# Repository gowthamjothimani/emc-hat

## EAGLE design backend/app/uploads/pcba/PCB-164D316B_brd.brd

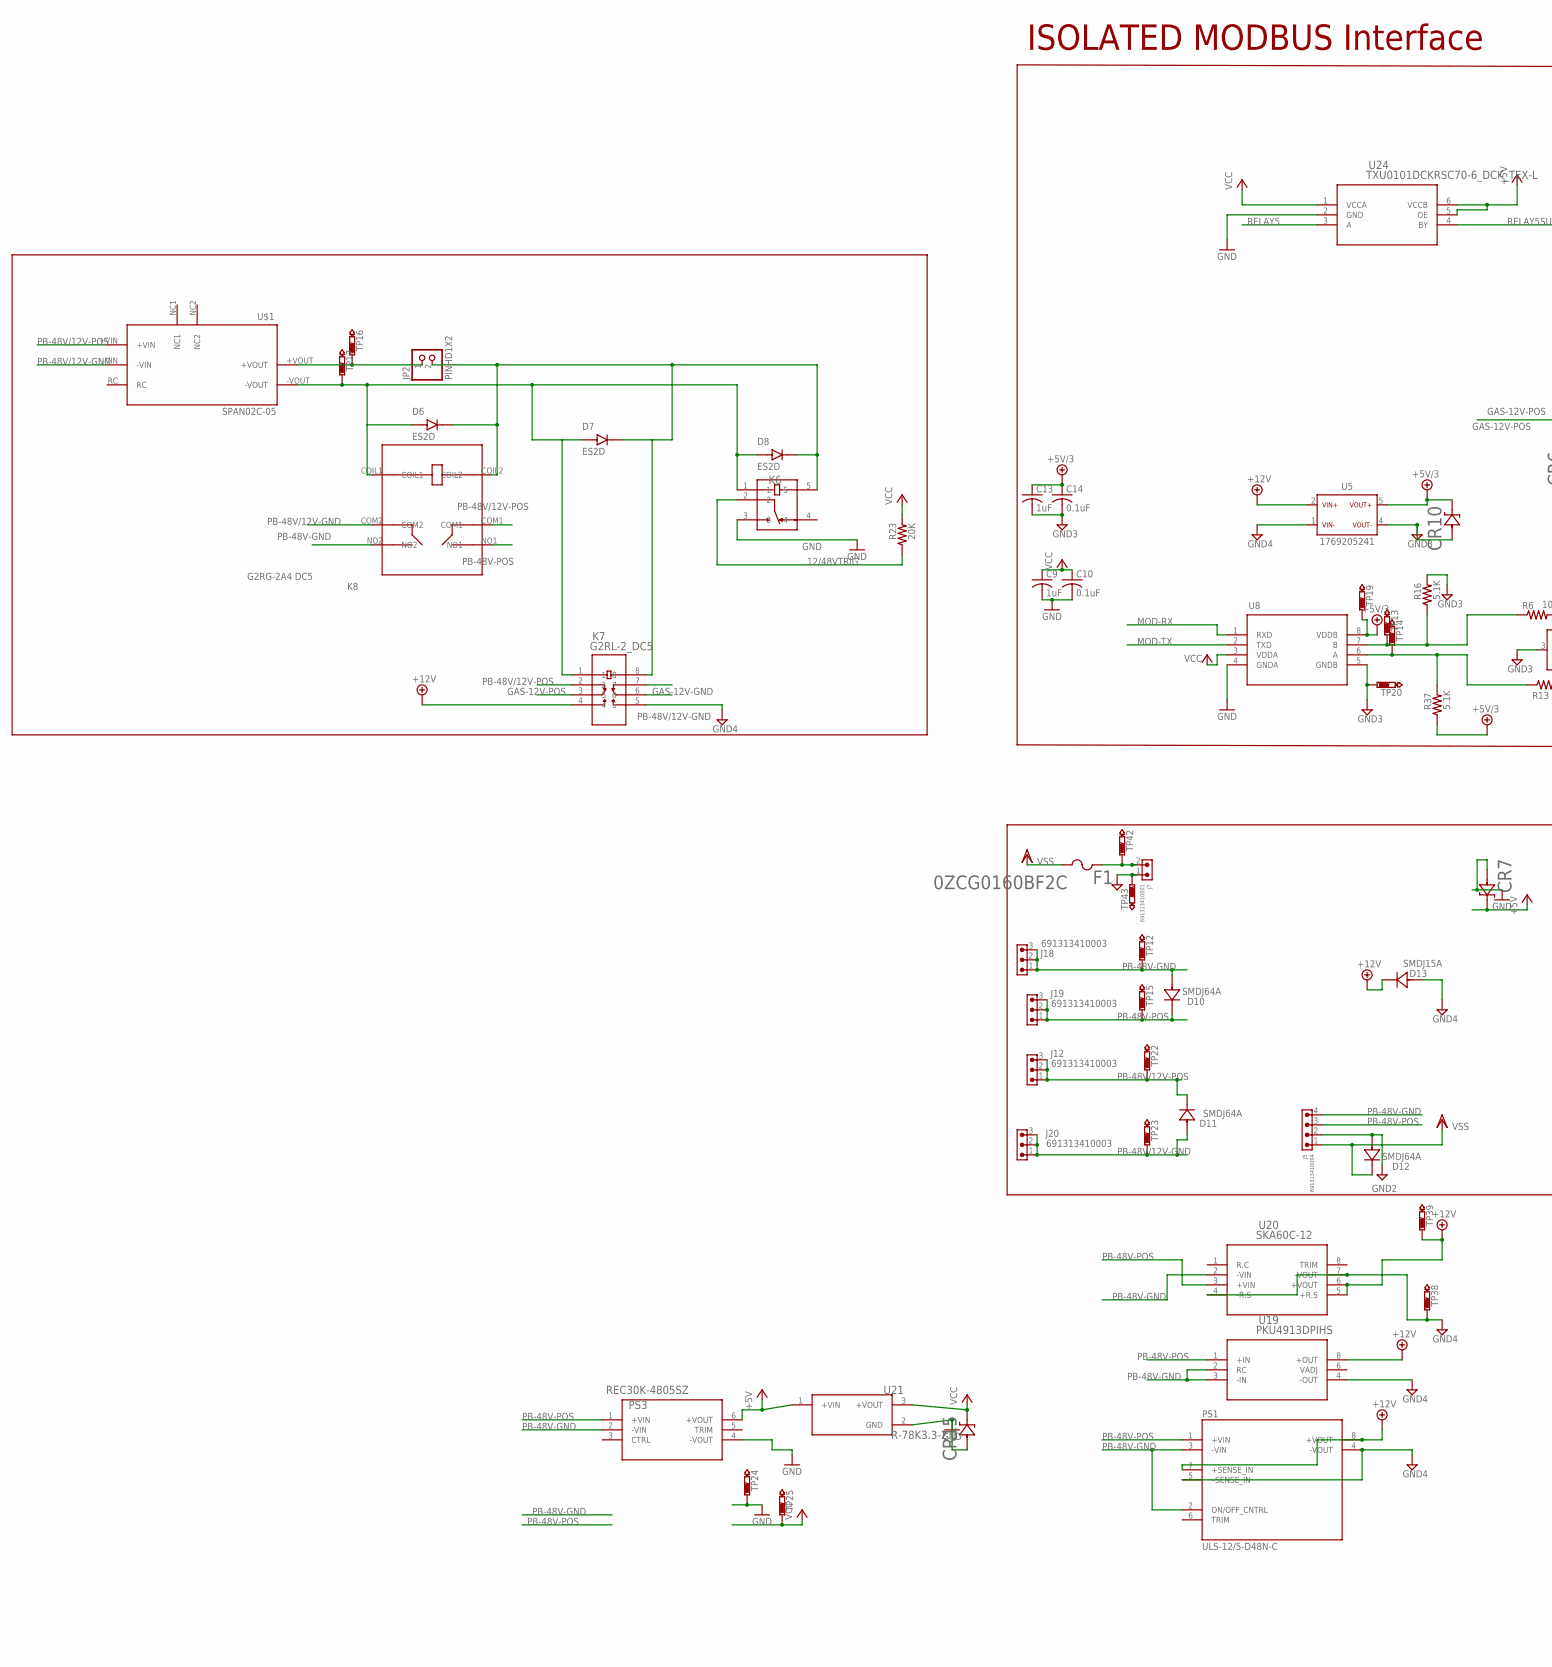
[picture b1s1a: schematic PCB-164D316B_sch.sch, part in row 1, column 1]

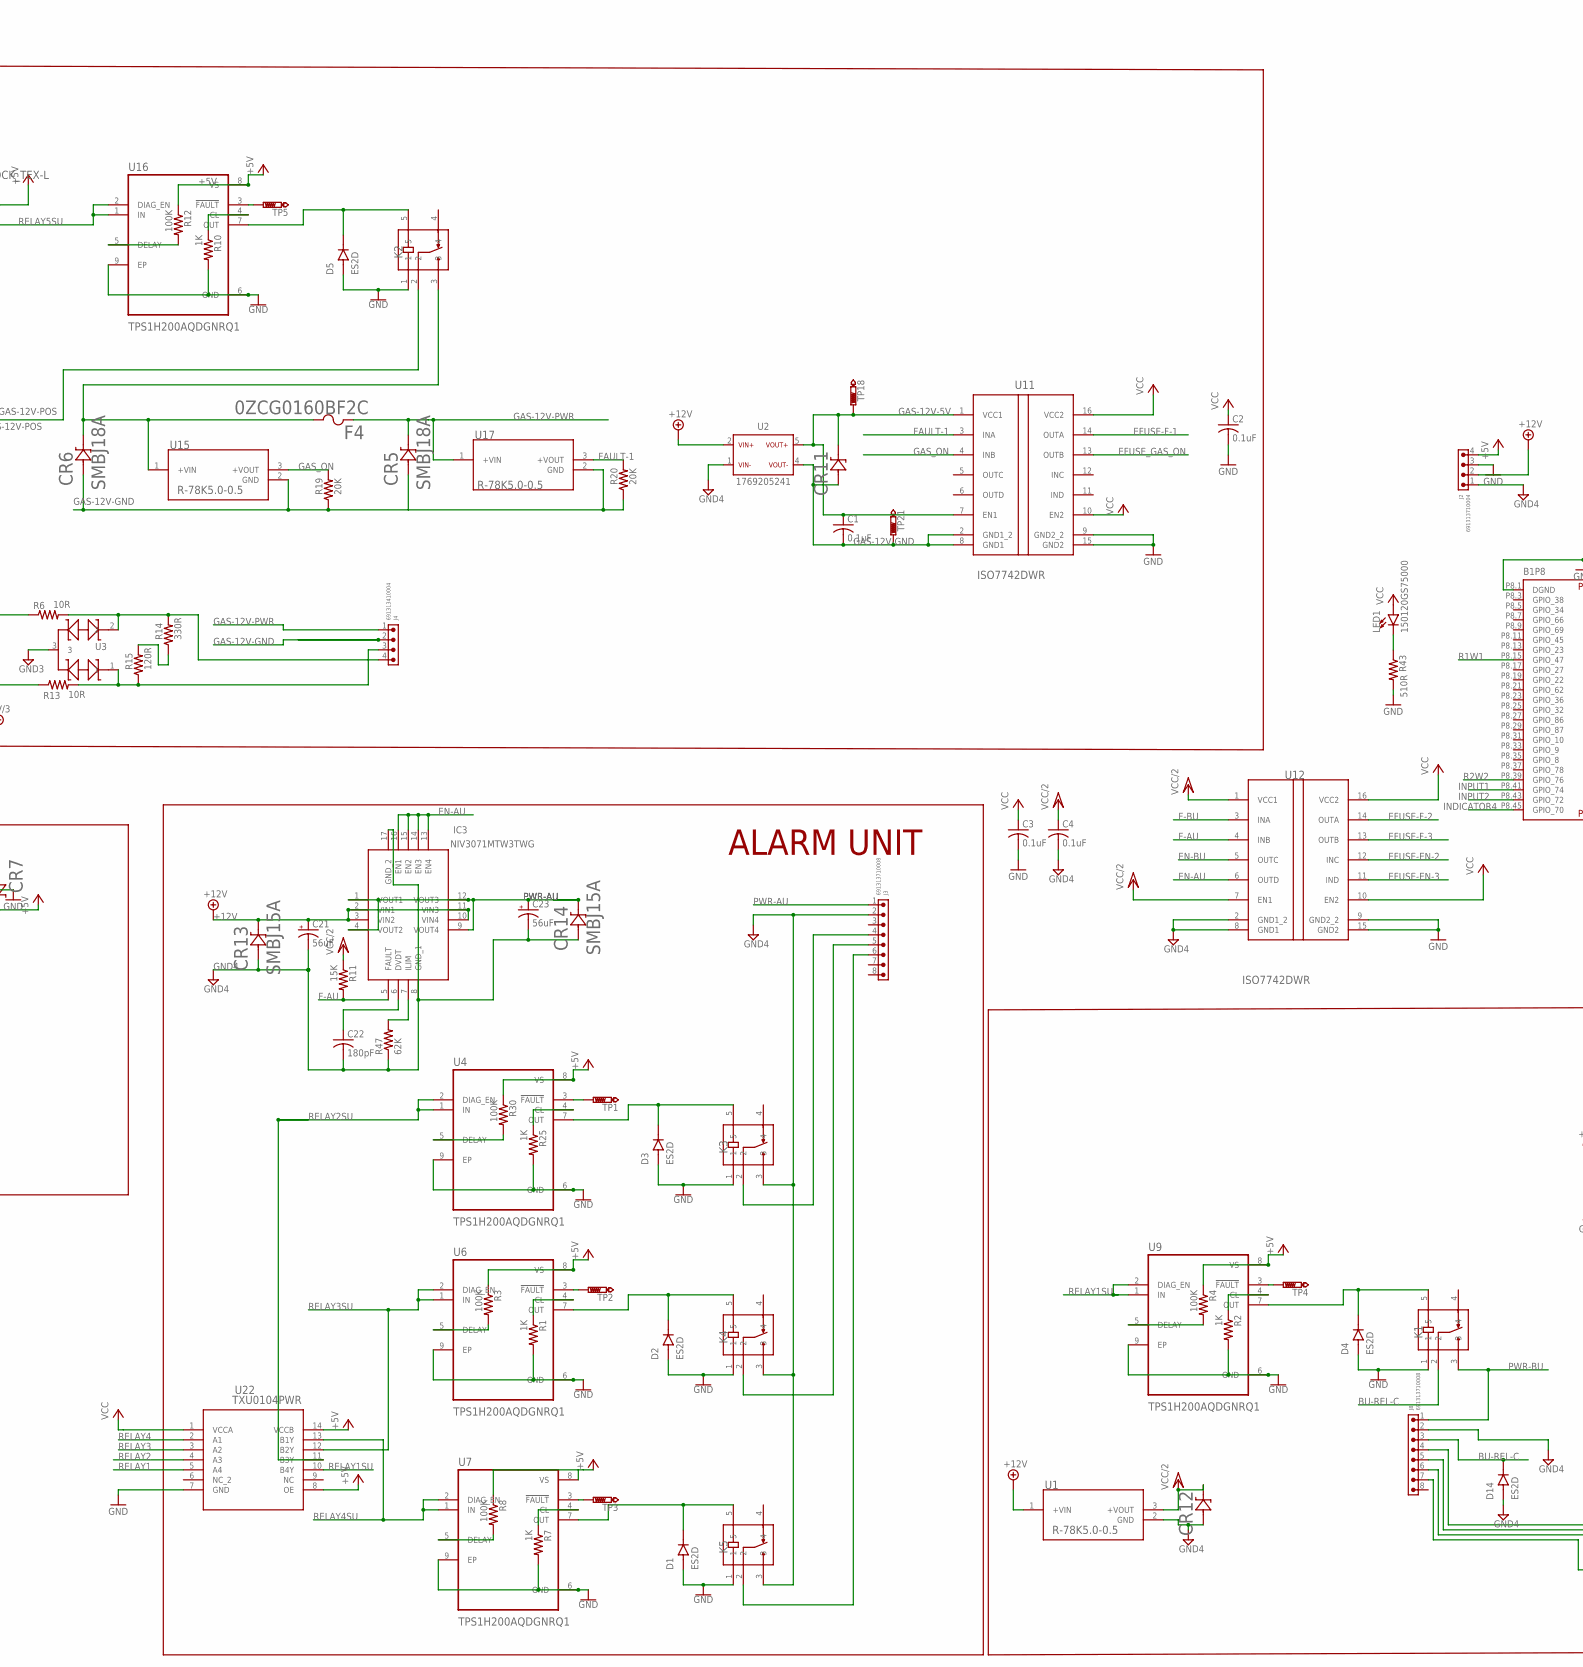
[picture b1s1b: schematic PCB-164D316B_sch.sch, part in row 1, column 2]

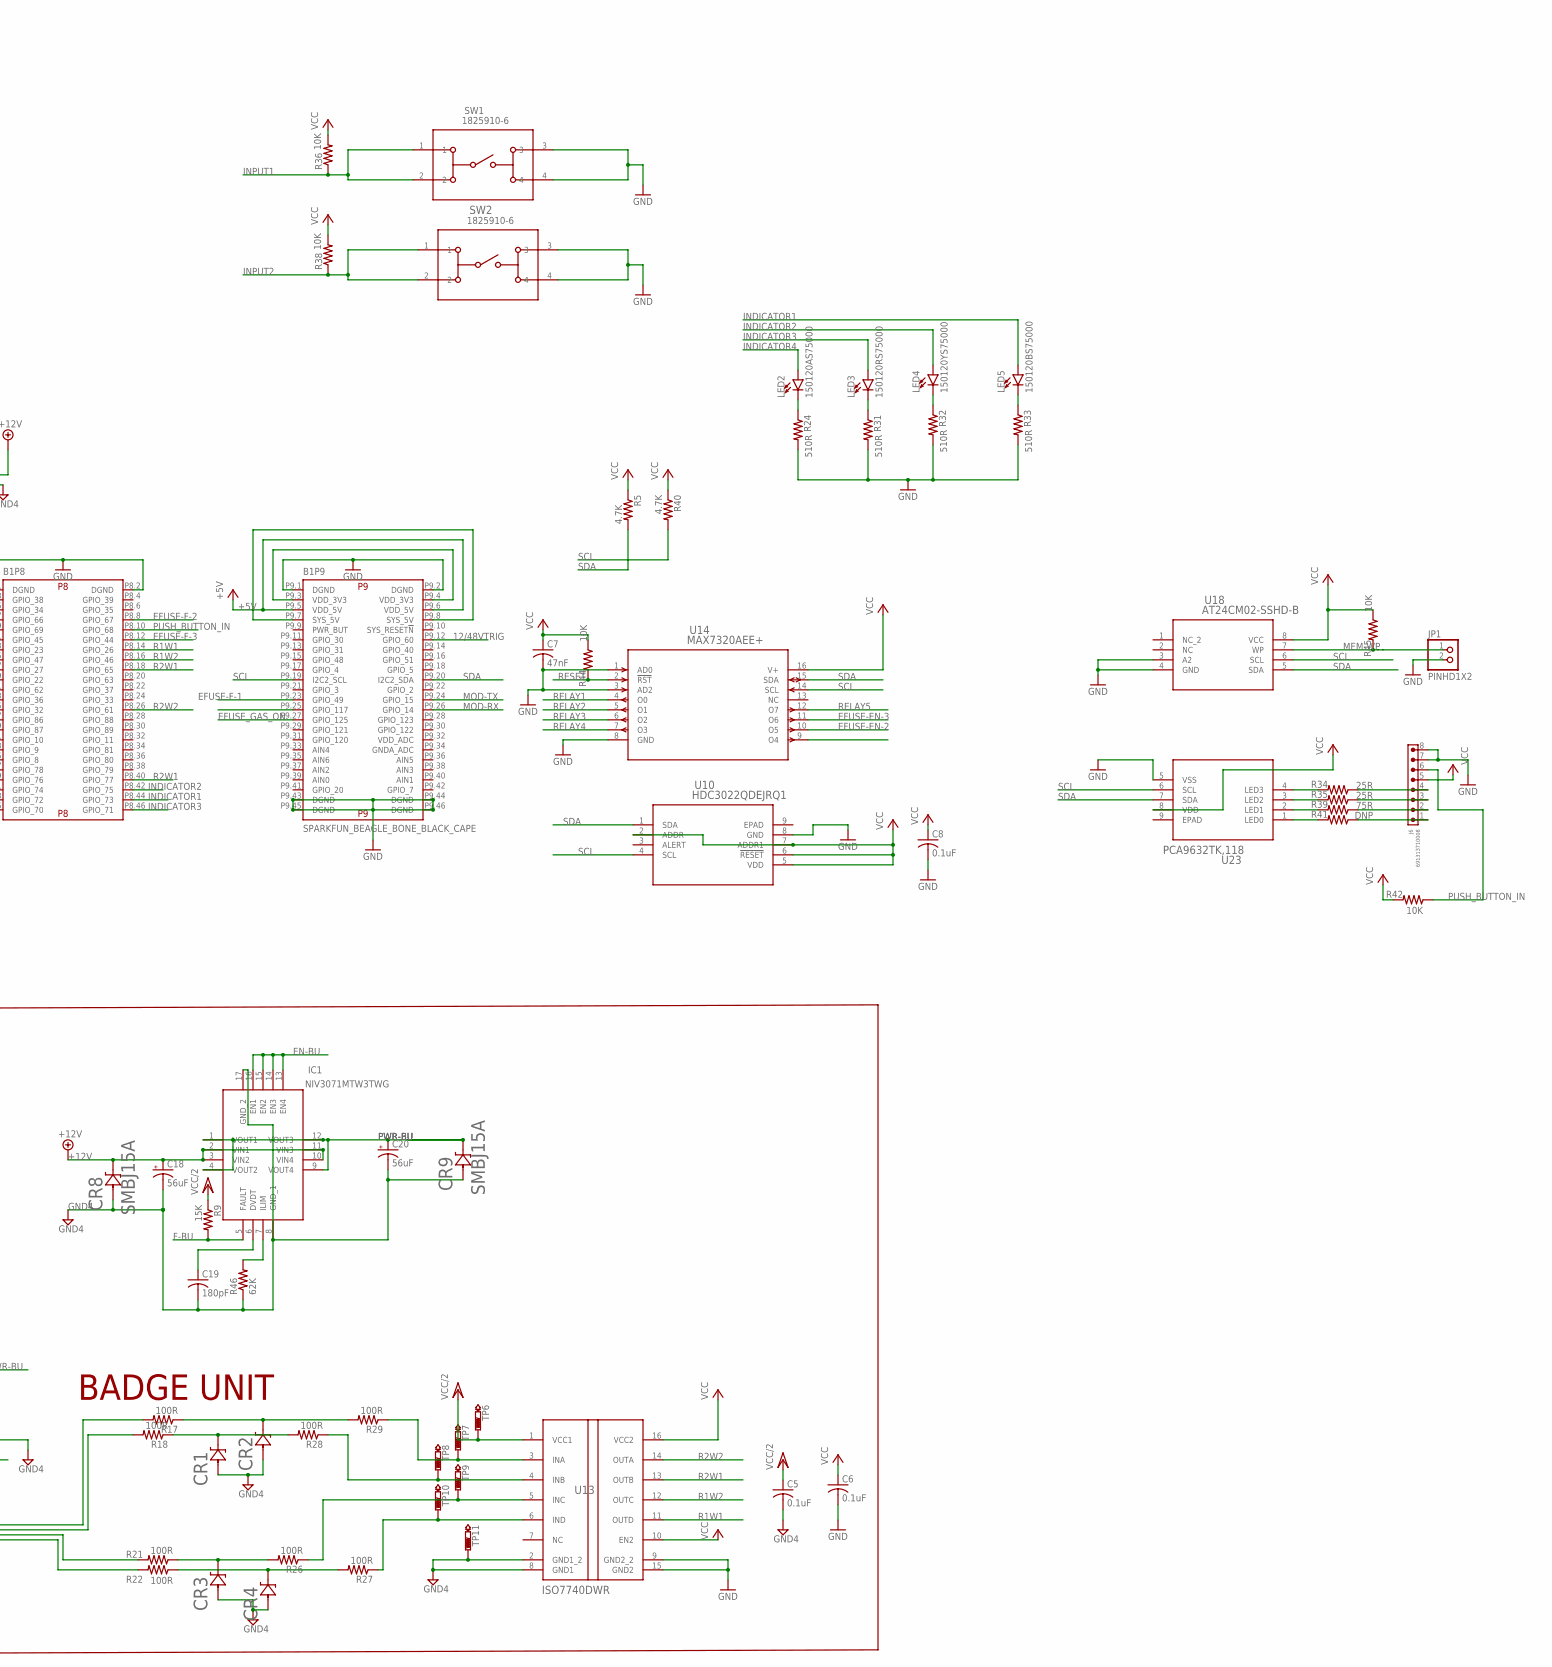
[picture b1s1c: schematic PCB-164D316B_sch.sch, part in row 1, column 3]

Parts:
B1: SPARKFUN_BEAGLE_BONE_BLACK_CAPE; BEAGLE_BONE_BLACK_CAPE
C1, C2, C3, C4, C5, C6, C8, C10, C14: 0.1uF; C1206
C7: 47nF; C1206
C9, C13: 1uF; C1206
C18, C20, C21, C23: 56uF; PANASONIC_C
C19, C22: 180pF; C1206
CR1, CR2, CR3, CR4, CR7, CR10, CR11, CR12, CR15: SMBJ6.0A; DO-214AA(SMB_J-BEND)_LTF-M
CR5, CR6: SMBJ18A; DO-214AA(SMB_J-BEND)_LTF-M
CR8, CR9, CR13, CR14: SMBJ15A; DO-214AA(SMB_J-BEND)_LTF-M
D1, D2, D3, D4, D5, D6, D7, D8, D14: ES2D; DIOM4336X265N
D10, D11, D12: SMDJ64A; SMDJSERIES_LTF-M
D13: SMDJ15A; SMDJSERIES_LTF-M
F1, F4: 0ZCG0160BF2C; 0ZCG_BEL
IC1, IC3: NIV3071MTW3TWG; QFN105P500X600X80-17N
J2: 691313710004
J3, J6, J8: 691313710008
J4, J5: 691313410004
J7: 691313410002
J12, J18, J19, J20: 691313410003
JP1, JP2: PINHD1X2; 1X02
K1, K2, K3, K4, K5, K6: G5Q-14_DC5; RELAY_G5Q-1_DC5_OMR
K7: G2RL-2_DC5; RELAY_G2RL-2_OMR
K8: G2RG-2A4 DC5; G2RG-2A4
LED1: 150120GS75000; LED-1206
LED2: 150120AS75000; LED-1206
LED3: 150120RS75000; LED-1206
LED4: 150120YS75000; LED-1206
LED5: 150120BS75000; LED-1206
PS1: ULS-12/5-D48N-C; CONV_ULS-12/5-D48N-C
PS3: REC30K-4805SZ; REC20K_RCP
R1, R2, R7, R10, R25: 1K; R1206
R3, R4, R8, R12, R30: 100K; R1206
R5, R40: 4.7K; R1206
R6, R13: 10R; R1206
R9, R11: 15K; R1206
R14: 330R; R1206
R15: 120R; R1206
R16, R37: 5.1K; R1206
R17, R18, R21, R22, R26, R27, R28, R29: 100R; R1206
R19, R20, R23: 20K; R1206
R24, R31, R32, R33, R43: 510R; R1206
R34, R35: 25R; R1206
R36, R38, R42, R44, R45: 10K; R1206
R39: 75R; R1206
R41: DNP; R1206
R46, R47: 62K; R1206
SW1, SW2: 1825910-6; SW4_1825910-B_TEC
TP1, TP2, TP3, TP4, TP5, TP6, TP7, TP8, TP9, TP10, TP11, TP12, TP13, TP14, TP15, TP16, TP17, TP18, TP19, TP20, TP21, TP22, TP23, TP24, TP25, TP38, TP39, TP42, TP43: TH; SMALL-TH
U1, U15, U17: R-78K5.0-0.5; SIP3_R-78K-0.5_RCP
U2, U5: 1769205241; WPME-FISM_SMT-8_L13.2W11.4H7.25
U3: SM712.TCT; SOT23_SEM-M
U4, U6, U7, U9, U16: TPS1H200AQDGNRQ1; SOP65P490X110-9N
U8: MAX22026FAWA+; 21-0262_W8MS+1_ADI-M
U10: HDC3022QDEJRQ1; WSON8_DEJ_TEX-M
U11, U12: ISO7742DWR; DW0016B_HV
U13: ISO7740DWR; DW0016B_HV
U14: MAX7320AEE+; 21-0055H_16_MXM-M
U18: AT24CM02-SSHD-B; SOIC8_4P9X3P9MC_MCH-L
U19: PKU4913DPIHS; PKU4913DPIHS_FPM
U20: SKA60C-12; SKA60_MWU
U21: R-78K3.3-2.0; CONV_R-78K3.3-2.0
U22: TXU0104PWR; TSSOP_0104PWR_TEX-L
U23: PCA9632TK,118; HVSON8_3X3_NXP
U24: TXU0101DCKRSC70-6_DCK_TEX-L; SC70-6_DCK_TEX-L
U$1: SPAN02C-05; SPBW03G-12

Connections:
12/48VTRIG: B1.P9.12 (GPIO_60), K6.2, R23.1
+5V: B1.P9.5 (VDD_5V), B1.P9.6 (VDD_5V), CR7.1 (CATHODE), J2.4, PS3.6 (+VOUT), R3.1, R4.1, R8.1, R12.1, R30.1, U4.8 (VS), U6.8 (VS), U7.8 (VS), U9.8 (VS), U16.8 (VS), U21.1 (+VIN), U22.8 (OE), U22.14 (VCCB), U24.5 (OE), U24.6 (VCCB)
+5V/3: C13.1, C14.1, CR10.1 (CATHODE), R37.1, TP19.P$1, U5.5 (+VOUT), U8.8 (VDDB)
+12V: C18.+, C21.+, CR8.1 (CATHODE), CR13.1 (CATHODE), D13.1, IC1.2 (VIN1), IC1.3 (VIN2), IC1.10 (VIN4), IC1.11 (VIN3), IC3.2 (VIN1), IC3.3 (VIN2), IC3.10 (VIN4), IC3.11 (VIN3), J2.2, K7.4, PS1.7 (+SENSE_IN), PS1.8 (+VOUT), TP39.P$1, U1.1 (+VIN), U2.2 (+VIN), U5.2 (+VIN), U19.8 (+OUT), U20.5 (+R.S), U20.6 (+VOUT)
BU-REL-C: D14.C (K), J8.3, K1.2
EFUSE-EN-2: U12.12 (INC), U14.10 (O5)
EFUSE-EN-3: U12.11 (IND), U14.11 (O6)
EFUSE-F-1: B1.P9.23 (GPIO_49), U11.14 (OUTA)
EFUSE-F-2: B1.P8.8 (GPIO_67), U12.14 (OUTA)
EFUSE-F-3: B1.P8.12 (GPIO_44), U12.13 (OUTB)
EFUSE_GAS_ON: B1.P9.27 (GPIO_125), U11.13 (OUTB)
EN-AU: IC3.13 (EN4), IC3.14 (EN3), IC3.15 (EN2), IC3.16 (EN1), U12.6 (OUTD)
EN-BU: IC1.13 (EN4), IC1.14 (EN3), IC1.15 (EN2), IC1.16 (EN1), U12.5 (OUTC)
F-AU: IC3.5 (FAULT), R11.2, U12.4 (INB)
F-BU: IC1.5 (FAULT), R9.2, U12.3 (INA)
FAULT-1: R20.2, U11.3 (INA), U17.3 (+VOUT)
GAS-12V-5V: C1.1, CR11.1 (CATHODE), TP18.P$1, U2.5 (+VOUT), U11.1 (VCC1), U11.7 (EN1)
GAS-12V-GND: C1.2, CR5.2 (ANODE), CR6.2 (ANODE), CR11.2 (ANODE), J4.2, K7.6, R19.1, R20.1, TP21.P$1, U2.4 (-VOUT), U11.2 (GND1_2), U11.8 (GND1), U15.2 (GND), U17.2 (GND)
GAS-12V-POS: K2.2, K7.3
GAS-12V-PWR: CR5.1 (CATHODE), F4.1, J4.1, U17.1 (+VIN)
GAS_ON: R19.2, U11.4 (INB), U15.3 (+VOUT)
GND: B1.P8.1 (DGND), B1.P8.2 (DGND), B1.P9.1 (DGND), B1.P9.2 (DGND), B1.P9.43 (DGND), B1.P9.44 (DGND), B1.P9.45 (DGND), B1.P9.46 (DGND), C2.2, C3.2, C6.2, C7.2, C8.2, C9.2, C10.2, CR7.2 (ANODE), CR15.2 (ANODE), D1.A, D2.A, D3.A, D4.A, D5.A, J2.3, J6.7, J6.8, JP1.2, K1.1, K2.1, K3.1, K4.1, K5.1, K6.3, PS3.4 (-VOUT), R1.2, R2.2, R7.2, R10.2, R24.2, R25.2, R31.2, R32.2, R33.2, R43.2, SW1.3, SW1.4, SW2.3, SW2.4, TP24.P$1, U4.6 (GND), U4.9 (EP), U6.6 (GND), U6.9 (EP), U7.6 (GND), U7.9 (EP), U8.4 (GNDA), U9.6 (GND), U9.9 (EP), U10.8 (GND), U11.9 (GND2_2), U11.15 (GND2), U12.9 (GND2_2), U12.15 (GND2), U13.9 (GND2_2), U13.15 (GND2), U14.1 (AD0), U14.3 (AD2), U14.8 (GND), U16.6 (GND), U16.9 (EP), U18.3 (A2), U18.4 (GND), U21.2 (GND), U22.7 (GND), U23.5 (VSS), U24.2 (GND)
GND2: D12.2, J5.2, J7.1, TP43.P$1
GND3: C13.2, C14.2, CR10.2 (ANODE), R16.2, TP20.P$1, U3.3, U5.4 (-VOUT), U8.5 (GNDB)
GND4: C4.2, C5.2, C18.-, C19.2, C20.-, C21.-, C22.2, C23.-, CR1.2 (ANODE), CR2.2 (ANODE), CR3.2 (ANODE), CR4.2 (ANODE), CR8.2 (ANODE), CR9.2 (ANODE), CR12.2 (ANODE), CR13.2 (ANODE), CR14.2 (ANODE), D13.2, D14.A, IC1.8 (GND_1), IC1.17 (GND_2), IC3.8 (GND_1), IC3.17 (GND_2), J2.1, J3.2, J8.2, K3.3, K4.3, K5.3, K7.5, PS1.4 (-VOUT), PS1.5 (–SENSE_IN), R46.1, R47.1, TP11.P$1, TP38.P$1, U1.2 (GND), U2.1 (-VIN), U5.1 (-VIN), U12.2 (GND1_2), U12.8 (GND1), U13.2 (GND1_2), U13.8 (GND1), U19.4 (-OUT), U20.4 (-R.S), U20.7 (-VOUT)
INDICATOR1: B1.P8.44 (GPIO_73), LED5.A
INDICATOR2: B1.P8.42 (GPIO_75), LED4.A
INDICATOR3: B1.P8.46 (GPIO_71), LED3.A
INDICATOR4: B1.P8.45 (GPIO_70), LED2.A
INPUT1: B1.P8.41 (GPIO_74), R36.1, SW1.1, SW1.2
INPUT2: B1.P8.43 (GPIO_72), R38.1, SW2.1, SW2.2
MEM-WP: JP1.1, R45.2, U18.7 (WP)
MOD-RX: B1.P9.26 (GPIO_14), U8.1 (RXD)
MOD-TX: B1.P9.24 (GPIO_15), U8.2 (TXD)
unnamed: CR6.1 (CATHODE), F4.2, K2.3, U15.1 (+VIN)
unnamed: R2.1, U9.4 (CL)
unnamed: D3.C (K), K3.5, U4.7 (OUT)
unnamed: R1.1, U6.4 (CL)
unnamed: TP1.P$1, U4.3 (!FAULT)
unnamed: R28.1, TP8.P$1, U13.4 (INB)
unnamed: CR3.1 (CATHODE), R21.1, R26.2
unnamed: CR4.1 (CATHODE), R22.1, R27.2
unnamed: CR2.1 (CATHODE), R17.1, R29.2
unnamed: R29.1, TP7.P$1, U13.3 (INA)
unnamed: CR1.1 (CATHODE), R18.1, R28.2
unnamed: R4.2, U9.5 (DELAY)
unnamed: R6.1, R16.1, TP13.P$1, U8.7 (B)
unnamed: R14.1, R15.2
unnamed: TP4.P$1, U9.3 (!FAULT)
unnamed: R13.1, R37.2, TP14.P$1, U8.6 (A)
unnamed: J4.4, R6.2, R14.2, U3.2
unnamed: R10.1, U16.4 (CL)
unnamed: D1.C (K), K5.5, U7.7 (OUT)
unnamed: R12.2, U16.5 (DELAY)
unnamed: R3.2, U6.5 (DELAY)
unnamed: B1.P9.3 (VDD_3V3), B1.P9.4 (VDD_3V3)
unnamed: J3.6, K5.2
unnamed: B1.P9.7 (SYS_5V), B1.P9.8 (SYS_5V)
unnamed: J3.5, K4.2
unnamed: R26.1, TP9.P$1, U13.5 (INC)
unnamed: J3.4, K3.2
unnamed: D5.C (K), K2.5, U16.7 (OUT)
unnamed: D2.C (K), K4.5, U6.7 (OUT)
unnamed: R7.1, U7.4 (CL)
unnamed: C19.1, IC1.6 (DVDT)
unnamed: TP3.P$1, U7.3 (!FAULT)
unnamed: TP5.P$1, U16.3 (!FAULT)
unnamed: R27.1, TP10.P$1, U13.6 (IND)
unnamed: D6.A, D7.A, D8.A, K6.1, K7.1, K8.COIL1, TP17.P$1, U$1.-VOUT
unnamed: R8.2, U7.5 (DELAY)
unnamed: J8.4, R17.2
unnamed: J8.5, R18.2
unnamed: J8.6, R21.2
unnamed: J8.7, R22.2
unnamed: TP2.P$1, U6.3 (!FAULT)
unnamed: D4.C (K), K1.5, U9.7 (OUT)
unnamed: JP2.1, TP16.P$1, U$1.+VOUT
unnamed: IC1.7 (ILIM), R46.2
unnamed: J4.3, R13.2, R15.1, U3.1
unnamed: D6.C (K), D7.C (K), D8.C (K), JP2.2, K6.5, K7.8, K8.COIL2
unnamed: LED2.C, R24.1
unnamed: LED3.C, R31.1
unnamed: LED4.C, R32.1
unnamed: LED5.C, R33.1
unnamed: R25.1, U4.4 (CL)
unnamed: R30.2, U4.5 (DELAY)
unnamed: R34.2, U23.4 (LED3)
unnamed: R35.2, U23.3 (LED2)
unnamed: R39.2, U23.2 (LED1)
unnamed: R41.2, U23.1 (LED0)
unnamed: J6.4, R34.1
unnamed: LED1.C, R43.1
unnamed: J6.3, R35.1
unnamed: C22.1, IC3.6 (DVDT)
unnamed: IC3.7 (ILIM), R47.2
unnamed: J6.2, R39.1
unnamed: J6.1, R41.1
unnamed: F1.1, J7.2, TP42.P$1
PB-48V-GND: D10.2, J5.4, J18.1, J18.2, J18.3, K8.NO2, PS1.2 (ON/OFF_CNTRL), PS1.3 (-VIN), PS3.2 (-VIN), TP12.P$1, U19.2 (RC), U19.3 (-IN), U20.2 (-VIN)
PB-48V-POS: D10.1, J5.3, J19.1, J19.2, J19.3, K8.NO1, PS1.1 (+VIN), PS3.1 (+VIN), TP15.P$1, U19.1 (+IN), U20.3 (+VIN)
PB-48V/12V-GND: D11.2, J20.1, J20.2, J20.3, K7.7, K8.COM2, TP23.P$1, U$1.-VIN
PB-48V/12V-POS: D11.1, J12.1, J12.2, J12.3, K7.2, K8.COM1, TP22.P$1, U$1.+VIN
PUSH_BUTTON_IN: B1.P8.10 (GPIO_68), J6.6, R42.1
PWR-AU: C23.+, CR14.1 (CATHODE), IC3.1 (VOUT1), IC3.4 (VOUT2), IC3.9 (VOUT4), IC3.12 (VOUT3), J3.1
PWR-BU: C20.+, CR9.1 (CATHODE), IC1.1 (VOUT1), IC1.4 (VOUT2), IC1.9 (VOUT4), IC1.12 (VOUT3), J8.1, K1.3
R1W1: B1.P8.14 (GPIO_26), B1.P8.15 (GPIO_47), U13.11 (OUTD)
R1W2: B1.P8.16 (GPIO_46), U13.12 (OUTC)
R2W1: B1.P8.18 (GPIO_65), B1.P8.40 (GPIO_77), U13.13 (OUTB)
R2W2: B1.P8.26 (GPIO_61), B1.P8.39 (GPIO_76), U13.14 (OUTA)
RELAY1: U14.4 (O0), U22.5 (A4)
RELAY1SU: U9.1 (IN), U9.2 (DIAG_EN), U22.10 (B4Y)
RELAY2: U14.5 (O1), U22.4 (A3)
RELAY2SU: U4.1 (IN), U4.2 (DIAG_EN), U22.11 (B3Y)
RELAY3: U14.6 (O2), U22.3 (A2)
RELAY3SU: U6.1 (IN), U6.2 (DIAG_EN), U22.12 (B2Y)
RELAY4: U14.7 (O3), U22.2 (A1)
RELAY4SU: U7.1 (IN), U7.2 (DIAG_EN), U22.13 (B1Y)
RELAY5: U14.12 (O7), U24.3 (A)
RELAY5SU: U16.1 (IN), U16.2 (DIAG_EN), U24.4 (BY)
RESET: R44.2, U14.2 (!RST)
SCL: B1.P9.19 (I2C2_SCL), R40.2, U10.4 (SCL), U14.14 (SCL), U18.6 (SCL), U23.6 (SCL)
SDA: B1.P9.20 (I2C2_SDA), R5.2, U10.1 (SDA), U14.15 (SDA), U18.5 (SDA), U23.7 (SDA)
VCC: C2.1, C3.1, C6.1, C7.1, C8.1, C9.1, C10.1, CR15.1 (CATHODE), J6.5, LED1.A, R5.1, R23.2, R36.2, R38.2, R40.1, R42.2, R44.1, R45.1, TP25.P$1, U8.3 (VDDA), U10.2 (ADDR), U10.5 (VDD), U10.6 (!RESET), U10.7 (ADDR1), U11.10 (EN2), U11.16 (VCC2), U12.10 (EN2), U12.16 (VCC2), U13.10 (EN2), U13.16 (VCC2), U14.16 (V+), U18.8 (VCC), U21.3 (+VOUT), U22.1 (VCCA), U23.8 (VDD), U24.1 (VCCA)
VCC/2: C4.1, C5.1, CR12.1 (CATHODE), R9.1, R11.1, TP6.P$1, U1.3 (+VOUT), U12.1 (VCC1), U12.7 (EN1), U13.1 (VCC1)
VSS: D12.1, F1.2, J5.1

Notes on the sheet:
BADGE UNIT
ISOLATED MODBUS Interface
ALARM UNIT

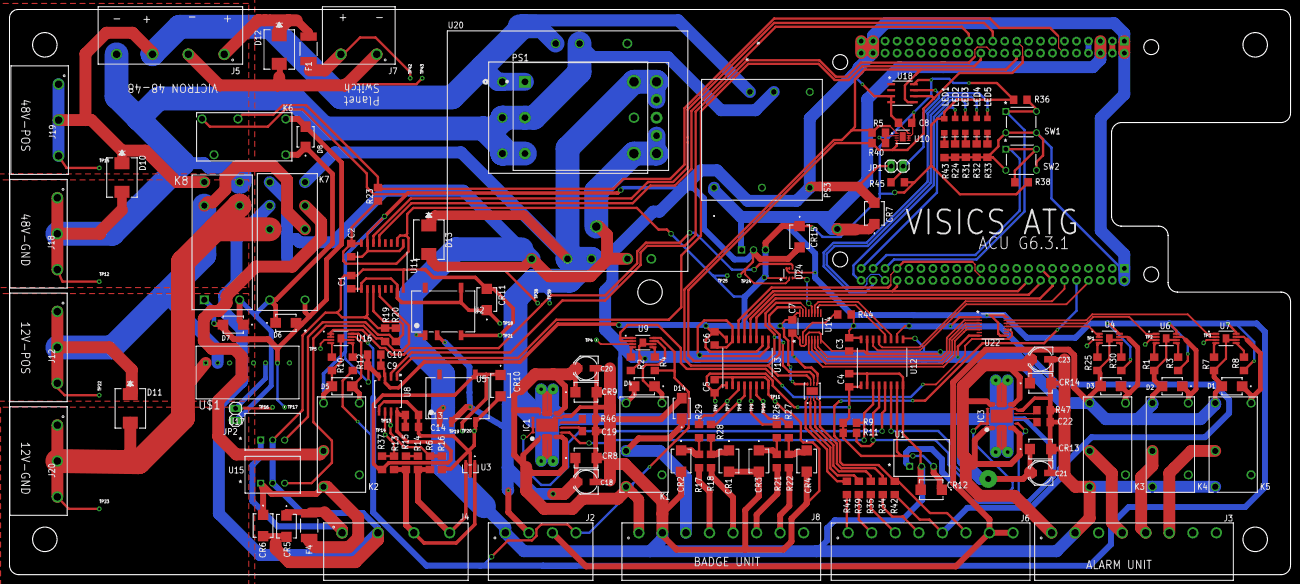
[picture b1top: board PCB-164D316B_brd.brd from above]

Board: 2 copper layers, 272.0 x 120.0 mm, 182 parts (1 on the bottom side), 125 nets.

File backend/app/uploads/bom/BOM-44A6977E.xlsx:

Part | Value | Device Count
U2, U5 | 1769205241 | 2
C1, C2, C3, C4, C5, C6, C8, C10, C14 | 0.1uF | 9
F1, F4 | 0ZCG0160BF2C | 2
R3, R4, R8, R12, R30 | 100K | 5
R17, R18, R21, R22, R26, R27, R28, R29 | 100R | 8
R36, R38, R42, R44, R45 | 10K | 5
R6, R13 | 10R | 2
R15 | 120R | 1
LED2 | 150120AS75000 | 1
LED5 | 150120BS75000 | 1
LED1 | 150120GS75000 | 1
LED3 | 150120RS75000 | 1
LED4 | 150120YS75000 | 1
R9, R11 | 15K | 2
C19, C22 | 180pF | 2
SW1, SW2 | 1825910-6 | 2
R1, R2, R7, R10, R25 | 1K | 5
C9, C13 | 1uF | 2
P8, P9 | 2076 | 2
R19, R20, R23 | 20K | 3
R34, R35 | 25R | 2
R14 | 330R | 1
R5, R40 | 4.7K | 2
C7 | 47nF | 1
R16, R37 | 5.1K | 2
R24, R31, R32, R33, R43 | 510R | 5
R46, R47 | 62K | 2
J7 | 691313410002 | 1
J12, J18, J19, J20 | 691313410003 | 4
J4, J5 | 691313410004 | 2
J2 | 691313710004 | 1
J3, J6, J8 | 691313710008 | 3
R39 | 75R | 1
U18 | AT24CM02-SSHD-B | 1
C18, C20, C21, C23 | EEE-FN1E560UR | 4
D1, D2, D3, D4, D5, D6, D7, D8, D14 | ES2D | 9
K8 | G2RG-2A4 DC5 | 1
K7 | G2RL-2 DC5 | 1
K1, K2, K3, K4, K5, K6 | G5Q-14 DC5 | 6
U10 | HDC3022QDEJRQ1 | 1
U13 | ISO7740DWR | 1
U11, U12 | ISO7742DWR | 2
U8 | MAX22026FAWA+ | 1
U14 | MAX7320AEE+ | 1
IC1, IC3 | NIV3071MTW3TWG | 2
U23 | PCA9632TK | 1
JP1, JP2 | PH1-02-UA | 2
U21 | R-78K3.3-2.0 | 1
U1, U15, U17 | R-78K5.0-0.5 | 3
PS3 | REC30K-4805SZ | 1
U20 | SKA60C-12 | 1
U3 | SM712.TCT | 1
CR8, CR9, CR13, CR14 | SMBJ15A | 4
CR5, CR6 | SMBJ18A | 2
CR1, CR2, CR3, CR4, CR7, CR10, CR11, CR12, CR15 | SMBJ6.0A | 9
D13 | SMDJ15A | 1
D10, D11, D12 | SMDJ64A | 3
U$1 | SPAN02C-05 | 1
U4, U6, U7, U9, U16 | TPS1H200AQDGNRQ1 | 5
U24 | TXU0101DCKR | 1
U22 | TXU0104PWR | 1
PS1 | ULS-12/5-D48N-C | 1
 | 0 | 0

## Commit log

2025-12-30 EMC - HAT v0.1 first commit
2025-12-30 EMC - HAT deployment script
2025-12-31 EMC - HAT Deployment v0.2
2025-12-31 EMC - HAT Deployment v0.3
2026-05-26 EMC - HAT Deployment v1.0.0
2026-05-26 Add React frontend files to repository

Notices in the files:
parts and their libraries:
SparkFun-Boards: Licensing: Creative Commons ShareAlike 4.0 International - https://creativecommons.org/licenses/by-sa/4.0
Eagle_MAGIC-FISM_rev22c: Copyright: Würth Elektronik
COPYRIGHT: Copyright (C) 2024 Ultra Librarian. All rights reserved.
